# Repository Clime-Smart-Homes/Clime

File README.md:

# Clime

Making smart homes smarter with machine learning. This project integrates machine learning algorithms on the NVIDIA Jetson with a Control4 Smart Home Controller to reduce water and electricity waste. 
Senior Capstone project for University of Utah ECE department, Fall 2022.

# Overview Diagram

Three different modules are present:
- *A.I. module* - Computer running computer vision models with a camera. We used a [NVIDIA Jetson Nano](https://developer.nvidia.com/embedded/jetson-nano-developer-kit) for this job.
- *Controller* - Smart home controller, here it is the [Control4 Controller](https://www.control4.com/solutions/products/controllers/).
- *Output* - Actuator that changes something in the home. In our case, it was a [smart faucet](https://github.com/Clime-Smart-Homes/Clime/tree/main/pcb/faucet/faucet) or standard light switch.

## Project hierarchy:
- [*src*](src) - All source code for connecting to Control4 director and running computer vision models.
- [*pcb*](pcb) - Diagrams and design documents for PCB built to convert Control4 outlet dimmer to 0-10V DC for faucet motors.
- [*venv*](venv) - Virtual Python 3.7 environment that should make setup easier.

## Team:
- Hibban Butt
- Zach Phelan

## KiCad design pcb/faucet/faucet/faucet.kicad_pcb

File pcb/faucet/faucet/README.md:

# Rectifer PCB
This PCB was designed in KiCAD. Use KiCAD to open `faucet.kicad_sch` or `fuacet.kicad_pcb` for changes. You may use the `gerbers.zip` file to print your own from any print shop that accepts gerber files. 
## PCB Diagram

This diagram shows the circuit diagram.

## Model and Traces

## Construced PCB

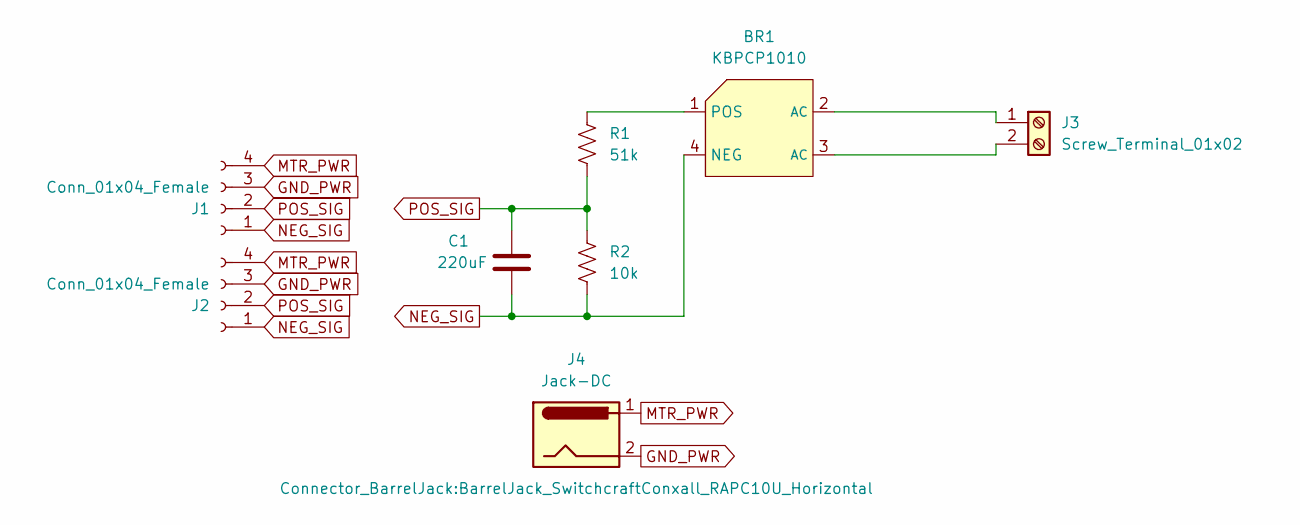
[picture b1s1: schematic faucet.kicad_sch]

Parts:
BR1: KBPCP1010; Rectifier KBPC1010
C1: 220uF; CP_Radial_D6.3mm_P2.50mm
J1, J2: Conn_01x04_Female; PinSocket_1x04_P2.54mm_Vertical
J3: Screw_Terminal_01x02; TerminalBlock_Altech_AK300-2_P5.00mm
J4: Jack-DC; BarrelJack_SwitchcraftConxall_RAPC10U_Horizontal
R1: 51k; R_Box_L8.4mm_W2.5mm_P5.08mm
R2: 10k; R_Box_L8.4mm_W2.5mm_P5.08mm

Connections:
GND_PWR: J1.3, J2.3, J4.2
MTR_PWR: J1.4, J2.4, J4.1
NEG_SIG: BR1.4 (NEG), C1.2, J1.1, J2.1, R2.2
unnamed: BR1.1 (POS), R1.1
unnamed: BR1.2 (AC), J3.1
unnamed: BR1.3 (AC), J3.2
POS_SIG: C1.1, J1.2, J2.2, R1.2, R2.1

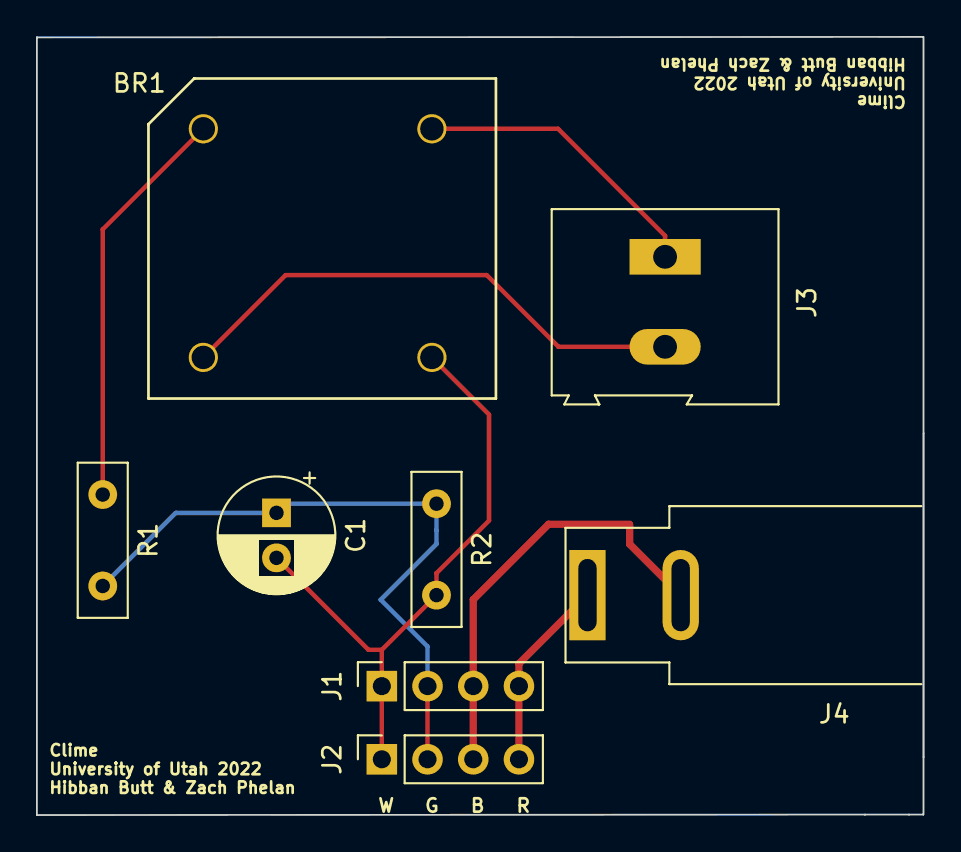
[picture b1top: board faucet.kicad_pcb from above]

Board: 2 copper layers, 49.2 x 43.2 mm, 8 parts (0 on the bottom side), 7 nets.

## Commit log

2022-09-01 Added project hierarchy
2022-09-13 Added first draft of PCB files
2022-09-13 Added .gitignore to ignore backups for KiCAD
2022-09-16 Added two OpenCV template programs to start with for face recognition and age recognition, adapted to work with a USB webcam.
2022-09-18 Finalize R and C values, add branding, ordered this board
2022-10-10 Refactor age prediction app to Control4 system, setup virutal env
2022-10-11 Reorganize project structure, make util libs, move to thread network calls
2022-10-15 Refactor folder structure, add emotion detection model
2022-10-31 Added emotion detection model
2022-10-31 Improved emotion detection output changing with emotion
2022-12-07 Add RESTful server, introduce env login
2022-12-12 Finalized version, improve UI for display
2022-12-12 Add READMEs w/ diagrams and structure (#1)
    * Update README.md
    * Add files via upload
    * Create README.md
    * Add files via upload
    * Delete pcb_diagram.png
    * Create README.md
